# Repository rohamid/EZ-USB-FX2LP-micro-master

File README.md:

# CY7C68013A QFN56 breakout board 
EZ-USB FX2LP QFN56 package on breadboard-friendly breakout board.

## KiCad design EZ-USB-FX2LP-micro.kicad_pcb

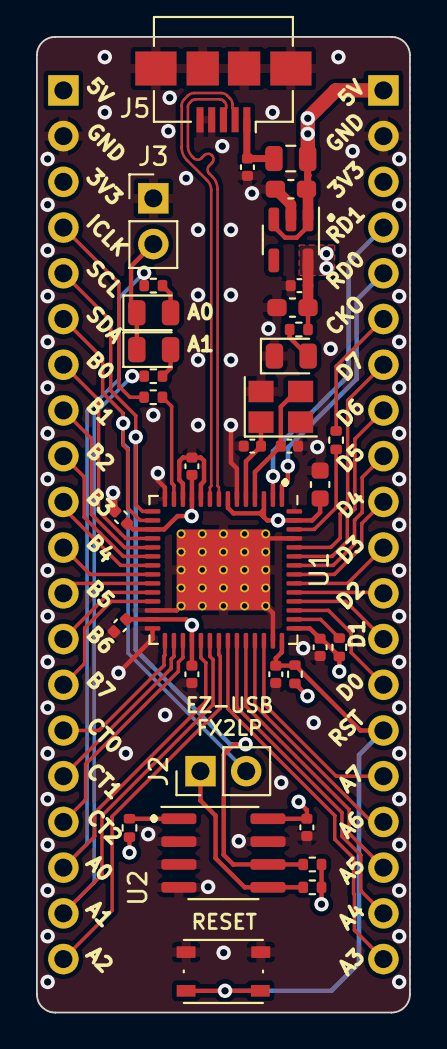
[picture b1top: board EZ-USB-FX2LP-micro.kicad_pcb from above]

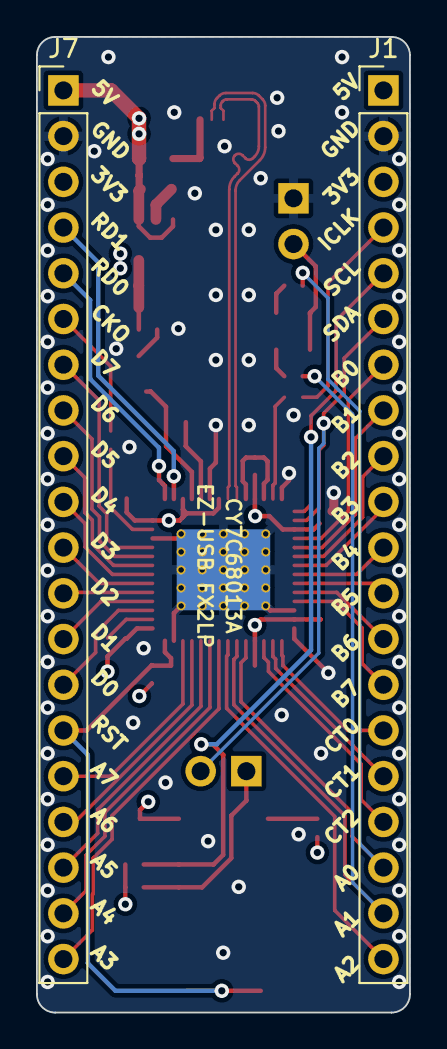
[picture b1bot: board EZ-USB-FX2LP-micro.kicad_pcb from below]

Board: 4 copper layers, 20.7 x 54.2 mm, 38 parts (2 on the bottom side), 51 nets.

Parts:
C1, C2: 14p; C_0402_1005Metric
C3, C4, C6, C7, C8, C9, C13, C14, C18: 100n; C_0402_1005Metric
C15: 1u; C_0603_1608Metric
C17: 2u2; C_0603_1608Metric_Pad1.08x0.95mm_HandSolder
C19: 4u7; C_0603_1608Metric_Pad1.08x0.95mm_HandSolder
D1: GREEN; LED_0805_2012Metric
D2, D3: RED; LED_0805_2012Metric
F1: 500mA; Fuse_0805_2012Metric
J1, J7: Conn_01x20; PinHeader_1x20_P2.54mm_Vertical
J2, J3: Conn_01x02; PinHeader_1x02_P2.54mm_Vertical
J5: USB_B_Micro; USB_Micro-B_Amphenol_10104110_Horizontal
R1, R8, R10: 10K; R_0402_1005Metric
R2, R3: 2K2; R_0402_1005Metric
R4, R5, R6: 1K; R_0402_1005Metric
R7, R9: 22; R_0402_1005Metric
SW1: SW_Push; SW_Push_1P1T_NO_Vertical_Wuerth_434133025816
U1: CY7C68013A-56LTX; QFN-56-1EP_8x8mm_P0.5mm_EP4.5x5.2mm_ThermalVias_TopTented
U2: 24LC64; SOIC-8_3.9x4.9mm_P1.27mm
U4: SPX3819M5-L-3-3; SOT-23-5
Y1: 24MHz'; Crystal_SMD_3225-4Pin_3.2x2.5mm

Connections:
+3V3: C3.1, C4.1, C6.1, C7.1, C8.1, C9.1, C15.1, C18.1, C19.1, J1.3, J7.3, R1.1, R2.1, R3.1, R4.1, R8.1, R10.1, U1.3 (AVCC), U1.7 (AVCC), U1.11 (VCC), U1.17 (VCC), U1.27 (VCC), U1.32 (VCC), U1.43 (VCC), U1.55 (VCC), U2.8 (VCC), U4.5 (OUT)
+5V: C17.1, F1.1, J1.1, J7.1, U4.1 (IN), U4.3 (EN)
/CLKOUT: J7.6, R7.2
/CTL0: J1.15, U1.29 (CTL0/FLAGA)
/CTL1: J1.16, U1.30 (CTL1/FLAGB)
/CTL2: J1.17, U1.31 (CTL2/FLAGC)
/D+: J5.3 (D+), U1.8 (D+)
/D-: J5.2 (D-), U1.9 (D-)
/IFCLK: J1.4, R9.2
/PA0: J1.18, R5.2, U1.33 (PA0/~INT0)
/PA1: J1.19, R6.2, U1.34 (PA1/~INT1)
/PA2: J1.20, U1.35 (PA2/SLOE)
/PA3: J7.20, U1.36 (PA3/WU2)
/PA4: J7.19, U1.37 (PA4/FIOADDR0)
/PA5: J7.18, U1.38 (PA5/FIOADDR1)
/PA6: J7.17, U1.39 (PA6/PKTEND)
/PA7: J7.16, U1.40 (PA7/FLAGD/~SLCS)
/PB0: J1.7, U1.18 (PB0/FD0)
/PB1: J1.8, U1.19 (PB1/FD1)
/PB2: J1.9, U1.20 (PB2/FD2)
/PB3: J1.10, U1.21 (PB3/FD3)
/PB4: J1.11, U1.22 (PB4/FD4)
/PB5: J1.12, U1.23 (PB5/FD5)
/PB6: J1.13, U1.24 (PB6/FD6)
/PB7: J1.14, U1.25 (PB7/FD7)
/PD0: J7.14, U1.45 (PD0/FD8)
/PD1: J7.13, U1.46 (PD1/FD9)
/PD2: J7.12, U1.47 (PD2/FD10)
/PD3: J7.11, U1.48 (PD3/FD11)
/PD4: J7.10, U1.49 (PD4/FD12)
/PD5: J7.9, U1.50 (PD5/FD13)
/PD6: J7.8, U1.51 (PD6/FD14)
/PD7: J7.7, U1.52 (PD7/FD15)
/RDY0: J7.5, U1.1 (RDY0/SLRD)
/RDY1: J7.4, U1.2 (RDY1/SLWR)
/SCL: J1.5, R3.2, U1.15 (SCL), U2.6 (SCL)
/SDA: J1.6, J2.2, U1.16 (SDA)
/WAKEUP: R10.2, U1.44 (WAKEUP)
/~RESET: C13.1, J7.15, R8.2, SW1.2, U1.42 (~RESET)
GND: C1.1, C2.1, C3.2, C4.2, C6.2, C7.2, C8.2, C9.2, C13.2, C14.2, C15.2, C17.2, C18.2, C19.2, D1.1 (K), J1.2, J3.1, J5.4 (ID), J5.5 (GND), J5.6 (Shield), J7.2, SW1.1, U1.6 (AGND), U1.10 (AGND), U1.12 (GND), U1.14 (RESERVED), U1.26 (GND), U1.28 (GND), U1.41 (GND), U1.53 (GND), U1.56 (GND), U1.57 (EP), U2.2 (A1), U2.3 (A2), U2.4 (GND), U2.7 (WP), U4.2 (GND), Y1.2, Y1.4
unnamed: D1.2 (A), R4.2
unnamed: D2.2 (A), R5.1
unnamed: D2.1 (K), D3.1 (K), J3.2
unnamed: D3.2 (A), R6.1
unnamed: J2.1, R2.2, U2.5 (SDA)
unnamed: R7.1, U1.54 (CLKOUT)
unnamed: R9.1, U1.13 (IFCLK)
unnamed: C2.2, U1.5 (XTALIN), Y1.1
unnamed: C1.2, U1.4 (XTALOUT), Y1.3
unnamed: R1.2, U2.1 (A0)
VBUS: C14.1, F1.2, J5.1 (VBUS)

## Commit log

2024-02-18 add README
